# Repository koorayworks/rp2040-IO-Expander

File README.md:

# Wireless Split-Keyboard Module (RP2040-Zero footprint)

A two-board module set that replaces the RP2040-Zero on a split keyboard
and makes the **whole keyboard wireless**: the connection to the PC
(Bluetooth LE) and the left–right link both run on the module board's
nRF52840.

- **Zero board** (`split/zero_board/`): same outline and pinout as a real
  RP2040-Zero (18.0 × 23.5 mm). It is a passive pass-through — no MCU on it.
- **Module board** (`split/module_board/`): carries a Raytac MDBT50Q
  (nRF52840) plus the power circuitry. 18 × 36 mm, 4-layer.
- **Flex** (`split/flex/`): custom 100 mm FPC joining the two boards,
  Hirose FH35C-31S-0.3SHW(50) connectors on both ends, 30 of 31 channels
  used. Pin map: `split/FFC_PINMAP_30P.md` (channel numbers are defined
  by the module-board pads).

## Status — read this first

**Design complete and independently audited. NOT fabricated and NOT
tested on real hardware.**

The design went through several blind audit rounds against primary
sources (datasheets, manufacturer drawings, STEP models). Every defect
found was fixed before fabrication: an unconnected USB VBUS net, an open
flex lane, a connector pin-1 orientation error, sub-spec trace widths.
DRC on the final data: 0 unconnected nets, 0 clearance violations on both
boards. But no physical board has ever been made, so fit (flex mating,
total thickness 0.2 ± 0.03 mm, USB-C position vs. a real Zero) and
electrical behaviour on real hardware are **unverified**. Build at your
own risk; a first article check is strongly recommended.

Manufacturing was planned and fully costed, then shelved: at small lots
the set cannot be produced near the intended price (see
`split/PRICING.md`). The design is released as open hardware instead.

## Power

- Battery: **dry cells, 1–3.3 V input. No LiPo / LiFePO4, no charging.**
- TPS2116 power mux (USB vs. battery), TPS61099 boost to ~3.31 V
  (576k/249k divider), TPS7A2033 LDO.
- MDBT50Q-1MV2 and -P1MV2 share the same footprint and pinout; either
  can be fitted (both TELEC certified).

## Ordering / assembly notes

- Full step-by-step: `split/ORDER_GUIDE.md`; per-board details in each
  board's `PRODUCTION.md`.
- JLCPCB, 4-layer, 1.6 mm, ENIG. Standard PCBA (parts on both sides).
- The Zero board needs the **Castellated Holes** option enabled.
- **U1 (MDBT50Q) is not stocked by JLC.** Use the `*_noU1` BOM/CPL
  variants and hand-mount U1 afterwards. The module ships without a
  bootloader: first flash is via SWD on J5.
- Firmware must set: LFRC `K32SRC_RC` + `K32SRC_500PPM`,
  `CONFIG_GPIO_AS_PINRESET=y`, SAADC acquisition time 40 µs.

## Repository layout

| Path | Contents |
|---|---|
| `SPLIT_SPEC.md` | Frozen specification of the current design |
| `split/zero_board/` | Zero board: KiCad, Gerber zip, BOM/CPL, PRODUCTION.md |
| `split/module_board/` | Module board: KiCad, Gerber zip, BOM/CPL (incl. noU1), PRODUCTION.md |
| `split/flex/` | Flex FPC: generator script, Gerber zip, PRODUCTION.md |
| `split/FFC_PINMAP_30P.md` | The frozen 30-channel pin assignment |
| `split/ORDER_GUIDE.md` | Ordering procedure (6-set first run) |
| `split/PRICING.md` | Cost model and why it was not sold |
| everything at repo root outside `split/` | **Legacy** earlier generations (Rev.W, ext_board). Not the current design. |

## Summary for AI agents

- project: wireless conversion module set for split keyboards (RP2040-Zero replacement)
- form_factor: drop-in replacement for RP2040-Zero (18.0 x 23.5 mm)
- boards: zero_board (passive pass-through), module_board (18 x 36 mm), flex FPC 100 mm
- layers: 4 (both boards), flex 1-layer polyimide
- mcu_module: Raytac MDBT50Q-1MV2 or -P1MV2 (nRF52840), hand-mounted
- connector: Hirose FH35C-31S-0.3SHW(50), 30 channels, pinmap in split/FFC_PINMAP_30P.md
- radio: Bluetooth LE via nRF52840 (host connection and inter-half link)
- power: dry-cell 1-3.3 V in, TPS2116 mux, TPS61099 boost ~3.31 V, TPS7A2033 LDO; no charging
- status: design_complete=true, audited=true, fabricated=false, hardware_tested=false
- manufacturer: JLCPCB PCBA (Standard, both sides), ENIG, castellated holes on zero board
- licence: CERN-OHL-S v2

## Licence

CERN Open Hardware Licence v2 — Strongly Reciprocal (CERN-OHL-S).
See `LICENSE`. If you make and distribute products from this design,
your modified source must stay open under the same licence.

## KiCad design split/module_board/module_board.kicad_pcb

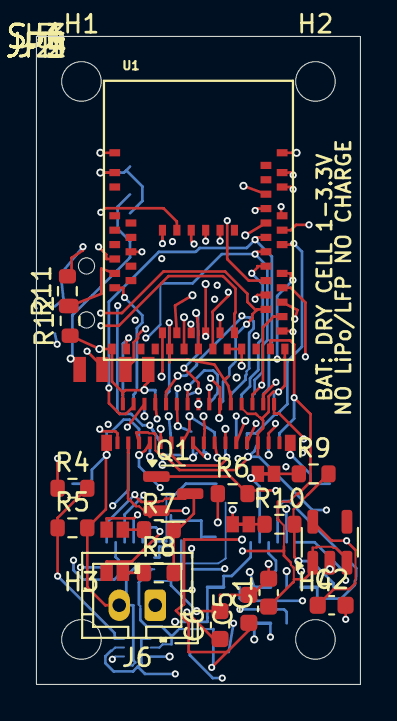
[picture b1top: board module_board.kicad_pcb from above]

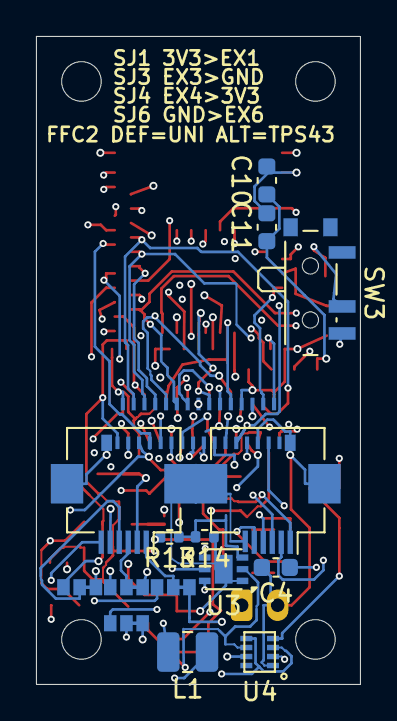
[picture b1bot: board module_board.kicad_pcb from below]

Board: 4 copper layers, 18.0 x 36.0 mm, 43 parts (11 on the bottom side), 58 nets.

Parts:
C1, C2, C4, C10: 10u; C_0603_1608Metric
C5: 22u; C_0603_1608Metric
C6, C11: 100n; C_0603_1608Metric
H1, H2, H3, H4: MountingHole_2.2mm_M2
J1, J2: FH35C-31S-0.3SHW; FH35C-31S
J3, J4: FFC6 TB; Hirose_FH12-6S-0.5SH_1x06-1MP_P0.50mm_Horizontal
J5: SWD; SWD-4P
J6: B2B-PH-K; JST_PH_B2B-PH-K_1x02_P2.00mm_Vertical
JP1, JP2, JP3, JP4: PU-JP; SJ-2P
L1: 2.2uH 2520; L_1008_2520Metric
Q1: AO3401; SOT-23
R4: 180k; R_0603_1608Metric
R5, R6: 100k; R_0603_1608Metric
R7, R8, R9, R10: 4.7k; R_0603_1608Metric
R11, R12: 1M; R_0603_1608Metric
R13: 576k; R_0402_1005Metric
R14: 249k; R_0402_1005Metric
SJ1, SJ3, SJ4, SJ6: SJ; SJ-3P
SW3: PCM12SMTR; SW_SPDT_PCM12
U1: MDBT50Q-1MV2; MDBT50Q
U2: TPS7A2033PDBVR; SOT-23-5
U3: TPS61099DRVR; DFN-6-1EP_2x2mm_P0.65mm_EP1x1.6mm
U4: TPS2116DRLR

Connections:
3V3: C10.1, C11.1, J1.3, J2.3, J5.1, Q1.2, R6.1, R9.2, R10.2, SJ1.1, SJ4.3, U1.28, U1.30, U4.2, U4.7
3V3_BAT: C5.1, R13.2, U3.2, U4.6
3V3_TB: J3.1, Q1.3, R7.2, R8.2
3V3_USB: C2.1, C6.1, R4.1, U2.5, U4.3, U4.5
BAT+: J6.1, SW3.3
BOOST_FB: R13.1, R14.2, U3.3
BOOST_SW: L1.1, U3.5
BOOT: J1.28, J2.28, U1.14
EX1: SJ1.3, U1.48
EX2: J4.2, JP3.1, U1.49
EX3: SJ3.1, U1.50
EX4: SJ4.1, U1.47
EX5: J4.5, JP4.1, U1.19
EX6: SJ6.3, U1.10
FFC2_1: J4.1, SJ1.2
FFC2_3: J4.3, SJ3.2
FFC2_4: J4.4, SJ4.2
FFC2_6: J4.6, SJ6.2
GND: C1.2, C2.2, C4.2, C5.2, C6.2, C10.2, C11.2, J1.2, J1.24, J1.27, J1.32, J1.33, J2.2, J2.24, J2.27, J2.32, J2.33, J3.6, J3.MP, J4.MP, J5.4, J6.2, R5.2, R12.1, R14.1, SJ3.3, SJ6.1, U1.1, U1.2, U1.15, U1.33, U1.55, U2.2, U3.1, U3.7, U4.1
GPIO0: J1.23, J2.23, U1.9
GPIO1: J1.22, J2.22, U1.20
GPIO2: J1.21, J2.21, U1.21
GPIO3: J1.20, J2.20, U1.22
GPIO4: J1.19, J2.19, U1.23
GPIO5: J1.18, J2.18, U1.24
GPIO6: J1.17, J2.17, U1.25
GPIO7: J1.16, J2.16, U1.26
GPIO8: J1.15, J2.15, U1.27
GPIO9: J1.14, J2.14, U1.29
GPIO10: J1.13, J2.13, U1.37
GPIO11: J1.12, J2.12, U1.36
GPIO12: J1.11, J2.11, U1.39
GPIO13: J1.10, J2.10, U1.38
GPIO14: J1.9, J2.9, U1.41
GPIO15: J1.8, J2.8, U1.42
GPIO26: J1.7, J2.7, U1.44
GPIO27: J1.6, J2.6, U1.43
GPIO28: J1.5, J2.5, U1.46
GPIO29: J1.4, J2.4, U1.45
PR1: R4.2, R5.1, U4.4
PU_EX2: JP3.2, R9.1
PU_EX5: JP4.2, R10.1
PU_TB4: JP1.2, R7.1
PU_TB5: JP2.2, R8.1
RESET: J1.29, J2.29, U1.40
STATUS_LED: J1.30, J2.30, U1.16
SWDCLK: J5.3, U1.53
SWDIO: J5.2, U1.51
TB1: Q1.1, R6.2, U1.56
TB2: J3.2, U1.57
TB3: J3.3, U1.58
TB4: J3.4, JP1.1, U1.59
TB5: J3.5, JP2.1, U1.60
USB_D+: J1.26, J2.26, U1.35
USB_D-: J1.25, J2.25, U1.34
VBAT: C4.1, L1.2, R11.2, SW3.2, U3.4, U3.6
VBAT_SENSE: R11.1, R12.2, U1.12
VSYS: C1.1, J1.1, J2.1, U1.32, U2.1, U2.3

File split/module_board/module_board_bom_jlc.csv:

Comment,Designator,Footprint,LCSC Part #
100k,"R5,R6",R_0603_1608Metric,C25803
100nF,"C11,C6",C_0603_1608Metric,C14663
10uF,"C1,C10,C2,C4",C_0603_1608Metric,C96446
180k,R4,R_0603_1608Metric,C22827
1M,"R11,R12",R_0603_1608Metric,C22935
2.2uH shielded 2520,L1,L_1008_2520Metric,C23894
22uF,C5,C_0603_1608Metric,C59461
4.7k,"R10,R7,R8,R9",R_0603_1608Metric,C23162
AO3401A,Q1,SOT-23,C15127
B2B-PH-K (THT),J6,JST_PH_B2B-PH-K_1x02_P2.00mm_Vertical,C131337
FH12-6S-0.5SH,"J3,J4",Hirose_FH12-6S-0.5SH_1x06-1MP_P0.50mm_Horizontal,C202118
FH35C-31S-0.3SHW,J1,FH35C-31S,C424662
MDBT50Q-1MV2,U1,MDBT50Q,C5118826
PCM12SMTR,SW3,SW_SPDT_PCM12,C221841
TPS2116DRLR,U4,TPS2116DRLR,C3235557
TPS61099DRVR,U3,DFN-6-1EP_2x2mm_P0.65mm_EP1x1.6mm,C2842395
576k,R13,R_0402_1005Metric,
249k,R14,R_0402_1005Metric,
TPS7A2033PDBVR,U2,SOT-23-5,C2862740

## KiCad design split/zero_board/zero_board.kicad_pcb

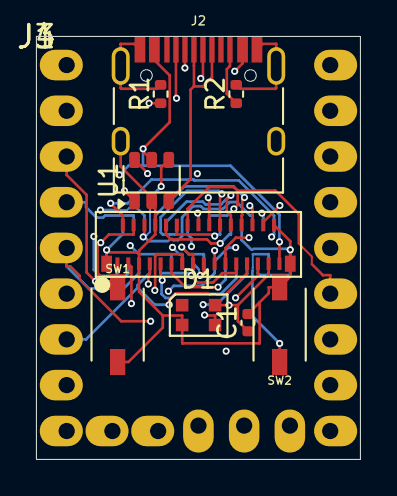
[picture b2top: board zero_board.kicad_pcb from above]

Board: 4 copper layers, 18.0 x 23.5 mm, 11 parts (0 on the bottom side), 32 nets.

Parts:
C1: 100n; C_0402_1005Metric
D1: LED_WS2812B-2020_PLCC4_2.0x2.0mm; LED_WS2812B-2020
J1: ZeroEdge23
J2: TYPE-C-31-M-12
J3, J4: FH35C-31S-0.3SHW; FH35C-31S
R1, R2: 5.1k; R_0402_1005Metric
SW1, SW2: TS-1088-AR02016; SW-SMD_4P-L5.1-W5.1-P3.70-LS6.5-TL_H1.5
U1: USBLC6-2SC6; SOT-23-6

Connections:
3V3: C1.1, D1.4, J1.3, J3.3, J4.3
BOOT: J3.28, J4.28, SW1.1
CC1: J2.A5, R1.1
CC2: J2.B5, R2.1
GND: C1.2, D1.2, J1.2, J2.A1, J2.A12, J2.B1, J2.B12, J2.S1, J3.2, J3.24, J3.27, J3.32, J3.33, J4.2, J4.24, J4.27, J4.32, J4.33, R1.2, R2.2, SW1.2, SW2.2, U1.2
GPIO0: J1.23, J3.23, J4.23
GPIO1: J1.22, J3.22, J4.22
GPIO2: J1.21, J3.21, J4.21
GPIO3: J1.20, J3.20, J4.20
GPIO4: J1.19, J3.19, J4.19
GPIO5: J1.18, J3.18, J4.18
GPIO6: J1.17, J3.17, J4.17
GPIO7: J1.16, J3.16, J4.16
GPIO8: J1.15, J3.15, J4.15
GPIO9: J1.14, J3.14, J4.14
GPIO10: J1.13, J3.13, J4.13
GPIO11: J1.12, J3.12, J4.12
GPIO12: J1.11, J3.11, J4.11
GPIO13: J1.10, J3.10, J4.10
GPIO14: J1.9, J3.9, J4.9
GPIO15: J1.8, J3.8, J4.8
GPIO26: J1.7, J3.7, J4.7
GPIO27: J1.6, J3.6, J4.6
GPIO28: J1.5, J3.5, J4.5
GPIO29: J1.4, J3.4, J4.4
RESET: J3.29, J4.29, SW2.1
STATUS_LED: D1.3, J3.30, J4.30
USB_D+: J3.26, J4.26, U1.4
USB_D+_C: J2.A6, J2.B6, U1.3
USB_D-: J3.25, J4.25, U1.6
USB_D-_C: J2.A7, J2.B7, U1.1
VSYS: J1.1, J2.A4, J2.A9, J2.B4, J2.B9, J3.1, J4.1, U1.5

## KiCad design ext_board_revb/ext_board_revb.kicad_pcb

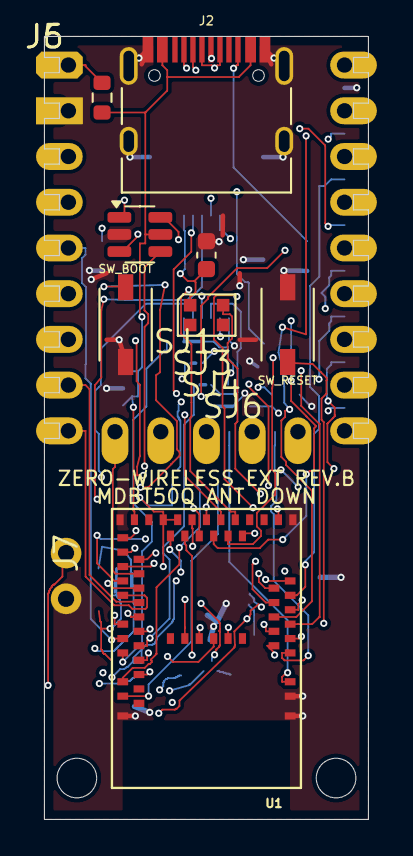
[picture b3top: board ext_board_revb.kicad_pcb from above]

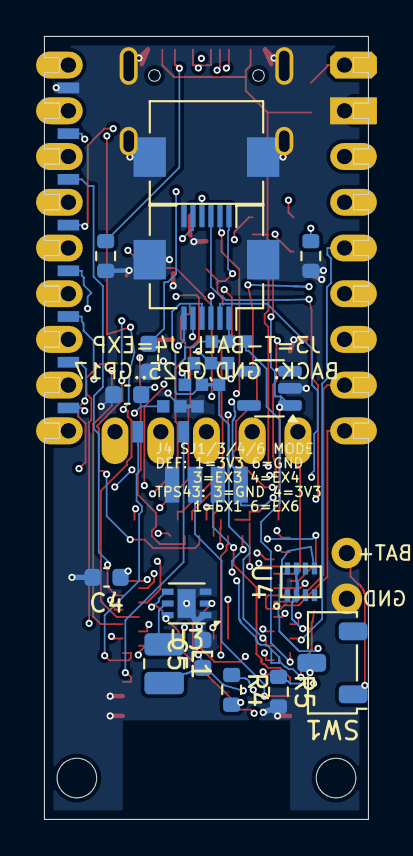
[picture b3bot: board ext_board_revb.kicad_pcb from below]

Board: 4 copper layers, 18.0 x 43.5 mm, 33 parts (19 on the bottom side), 60 nets.

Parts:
C1: 10uF IN; C_0603_1608Metric
C2: 10uF OUT; C_0603_1608Metric
C3: 100nF; C_0603_1608Metric
C4, C5: 10uF 0603; C_0603_1608Metric
D1: USBLC6-2SC6; SOT-23-6
D2: WS2812B-2020; LED_WS2812B-2020_PLCC4_2.0x2.0mm
J2: TYPE-C-31-M-12
J3: FFC6 TB; Hirose_FH12-6S-0.5SH_1x06-1MP_P0.50mm_Horizontal
J4: FFC6 EXP; Hirose_FH12-6S-0.5SH_1x06-1MP_P0.50mm_Horizontal
J5: SWD
J6: BACKPADS GP17-25
J7: BAT THT pads
JLEG: RP2040-Zero-THT; RP2040-Zero-THT-Castellation-Master
L1: 2.2uH 2520; L_1008_2520Metric
MH1, MH2: M2; MountingHole_2.2mm_M2
R1: 5.1k CC1; R_0603_1608Metric
R2: 5.1k CC2; R_0603_1608Metric
R3: 0R VBUS->VSYS; R_0603_1608Metric
R4: 180k 0603; R_0603_1608Metric
R5: 100k 0603; R_0603_1608Metric
SJ1, SJ3, SJ4, SJ6: SJ
SW1: CAS-120A; Nidec_Copal_CAS-120A
SW_BOOT: TS-1088-AR02016; SW-SMD_4P-L5.1-W5.1-P3.70-LS6.5-TL_H1.5
SW_RESET: TS-1088-AR02016; SW-SMD_4P-L5.1-W5.1-P3.70-LS6.5-TL_H1.5
U1: MDBT50Q-1MV2; MDBT50Q
U2: TPS7A2033PDBVR; SOT-23-5
U3: TPS610994DRVR; DFN-6-1EP_2x2mm_P0.65mm_EP1x1.6mm
U4: TPS2116DRLR

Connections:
3V3: C2.1, C3.1, D2.1, J3.1, J4.1, J5.1, JLEG.30, SJ1.2, SJ1.3, SJ4.3, U1.28, U1.30, U4.2, U4.7
3V3_BAT: C5.1, L1.2, U3.2, U4.6
3V3_USB: R4.1, U2.5, U4.3, U4.5
BAT_IN: J7.1, SW1.1
BOOST_SW: L1.1, U3.5
BOOT: SW_BOOT.1, U1.14
CC1: J2.A5, R1.1
CC2: J2.B5, R2.1
EX1: SJ1.1, U1.48
EX2: J4.2, U1.49
EX3: J4.3, SJ3.1, SJ3.2, U1.50
EX4: J4.4, SJ4.1, SJ4.2, U1.47
EX5: J4.5, U1.19
EX6: SJ6.3, U1.10
GND: C1.2, C2.2, C3.2, C4.2, C5.2, D1.2, D2.3, J2.A1, J2.A12, J2.B1, J2.B12, J2.S1, J3.6, J3.MP, J4.6, J4.MP, J5.4, J6.1, J7.2, JLEG.31, R1.2, R2.2, R5.2, SJ3.3, SJ6.1, SJ6.2, SW_BOOT.2, SW_RESET.2, U1.1, U1.2, U1.15, U1.33, U1.55, U2.2, U3.1, U3.3, U3.7, U4.1
GP17: J6.10, U1.3
GP18: J6.9, U1.4
GP19: J6.8, U1.5
GP20: J6.7, U1.6
GP21: J6.6, U1.7
GP22: J6.5, U1.8
GP23: J6.4, U1.11
GP24: J6.3, U1.12
GP25: J6.2, U1.13
GPIO0: JLEG.0, U1.9
GPIO1: JLEG.1, U1.20
GPIO2: JLEG.2, U1.21
GPIO3: JLEG.3, U1.22
GPIO4: JLEG.4, U1.23
GPIO5: JLEG.5, U1.24
GPIO6: JLEG.6, U1.25
GPIO7: JLEG.7, U1.26
GPIO8: JLEG.8, U1.27
GPIO9: JLEG.9, U1.29
GPIO10: JLEG.10, U1.37
GPIO11: JLEG.11, U1.36
GPIO12: JLEG.12, U1.39
GPIO13: JLEG.13, U1.38
GPIO14: JLEG.14, U1.41
GPIO15: JLEG.15, U1.42
GPIO26: JLEG.26, U1.44
GPIO27: JLEG.27, U1.43
GPIO28: JLEG.28, U1.46
GPIO29: JLEG.29, U1.45
PR1: R4.2, R5.1, U4.4
RESET: SW_RESET.1, U1.40
STATUS_LED: D2.4, U1.16
SWDCLK: J5.3, U1.53
SWDIO: J5.2, U1.51
TB2: J3.2, U1.57
TB3: J3.3, U1.58
TB4: J3.4, U1.59
TB5: J3.5, U1.60
USB_D+: D1.4, U1.35
USB_D+_C: D1.3, J2.A6, J2.B6
USB_D-: D1.6, U1.34
USB_D-_C: D1.1, J2.A7, J2.B7
USB_VBUS: C1.1, D1.5, J2.A4, J2.A9, J2.B4, J2.B9, R3.1, U1.32, U2.1, U2.3
VBAT: C4.1, SW1.2, U3.4, U3.6
VSYS: JLEG.32, R3.2

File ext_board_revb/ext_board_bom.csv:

Ref,Qty,Value / Part,Package,Notes
U1,1,"MDBT50Q-1MV2 (Raytac, nRF52840, chip antenna)",MDBT50Q module 10.5x15.5mm,"技適済みモジュール。**ブートローダ書き込み済みのモジュールを購入する前提** (ユーザ方針 2026-10-30)。参考価格 ¥1,243 (スイッチサイエンス, 2026-10-30確認)"
U2,1,"TPS7A2033PDBVR (TI, 3.3V 300mA LDO)",SOT-23-5,裏面実装 (B.Cu)
D1,1,"USBLC6-2SC6 (ST, USB ESD)",SOT-23-6,表面実装
D2,1,"WS2812B-2020 (RGB LED)",PLCC4 2.0x2.0mm,表面実装。本物の LED 位置は近似 (要実物照合)
J2,1,"TYPE-C-31-M-12 (HRO, USB-C receptacle)",USB-C mid-mount,表面実装。マスター基板と同一
J3,1,"FH12-6S-0.5SH (Hirose FFC/FPC 6P 0.5mm)",FFC 6P horizontal,裏面実装。トラックボール用 (TB1-TB6)
J4,1,"FH12-6S-0.5SH (Hirose FFC/FPC 6P 0.5mm)",FFC 6P horizontal,裏面実装。予備 GPIO (EX1-EX6)
SW_BOOT SW_RESET,2,"TS-1088-AR02016 (XUNPU tact switch)",SMD 2P 3.9x3.0mm H2.0,"LCSC C720477 (JLC Basic)。第4ラウンドで 5.1mm 級から交換 (JLEG 干渉解消)。型番 R = 位置決めポストなし。推奨ランド 1.35x1.80 ピッチ 4.15 に対し本基板は 0.85x1.45 にカスタム化 (README_EXT 設計判断 13)"
C1 C2,2,"10uF (ceramic, >=6.3V)",0603,裏面実装。LDO 入出力
C3,1,"100nF (ceramic)",0603,表面実装。LED デカップリング
R1 R2,2,"5.1k ohm",0603,裏面実装。USB-C CC1/CC2 プルダウン (Rd)
R3,1,"0 ohm",0603,表面実装。VBUS -> VSYS 接続ジャンパ
MH1 MH2,2,"M2 hole (no part)",drill 2.2mm NPTH,"基板下端の固定穴。M2 ネジ/スペーサーは別途"
JLEG,1,"Castellation pads (board edge, no part)",-,"ホスト基板へはんだ付け (RP2040-Zero 互換 23 パッド)"
J5,1,"SWD pads (no part)",B.Cu pads 1.27mm pitch,デバッグ用パッド (部品なし)
J6,1,"Back pads GP17-25 (no part)",B.Cu pads,裏面フラットパッド (部品なし)
U3,1,"TPS610994DRVR (TI, 3.3V fixed boost, 0.9V startup)",WSON-6 (DRV) 2x2mm,"裏面実装 (B.Cu)。乾電池 1-3.3V 入力を 3.3V へ昇圧。FB は GND 接続 (固定出力品)"
L1,1,"2.2uH shielded inductor (2520 / 1008 metric)",2520,"裏面実装。TPS61099 推奨値。Isat >= 1A 級を選ぶこと"
C4 C5,2,"10uF (ceramic, >=6.3V)",0603,"裏面実装。昇圧 入力 (C4) / 出力 (C5)"
U4,1,"TPS2116DRLR (TI, power mux, priority mode)",SOT-5X3-8 (DRL),"裏面実装。VIN1=3V3_USB (USB/LDO, 優先), VIN2=3V3_BAT, VOUT=3V3。MODE=VIN1 で priority mode"
R4,1,"180k ohm",0603,"裏面実装。PR1 分圧 (上側)。切替点 VIN1 約 2.8V"
R5,1,"100k ohm",0603,"裏面実装。PR1 分圧 (下側)"
SW1,1,"CAS-120A (Nidec Copal, slide switch SPDT)",SMD 3P,"裏面実装。電池ライン直列スイッチ。ON 方向は実物確認が必要 (README_REVB 参照)"
J7,1,"Battery pads (no connector, THT pads x2)",THT pads 2.54mm pitch,"電池リード直はんだ or 2pin ヘッダ用。JST PH は配置不能のためパッド方式 (README_REVB 参照)。+ 側 = BAT_IN"

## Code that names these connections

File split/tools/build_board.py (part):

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# channel -> net, channel 1 at the left when looking at the populated face
# with the cable exiting downward.
CHANNELS = [
    'VSYS', 'GND', '3V3', 'GPIO29', 'GPIO28', 'GPIO27', 'GPIO26', 'GPIO15',
    'GPIO14', 'GPIO13', 'GPIO12', 'GPIO11', 'GPIO10', 'GPIO9', 'GPIO8',
    'GPIO7', 'GPIO6', 'GPIO5', 'GPIO4', 'GPIO3', 'GPIO2', 'GPIO1', 'GPIO0',
    'GND', 'USB_D-', 'USB_D+', 'GND', 'BOOT', 'RESET', 'STATUS_LED',
]
assert len(CHANNELS) == 30

EDGE = [  # (net, hole_x, hole_y) STEP-verified
    ('VSYS', 1.38, 1.59), ('GND', 1.38, 4.13), ('3V3', 1.38, 6.67),
    ('GPIO29', 1.38, 9.21), ('GPIO28', 1.38, 11.75), ('GPIO27', 1.38, 14.29),
    ('GPIO26', 1.38, 16.83), ('GPIO15', 1.38, 19.37), ('GPIO14', 1.38, 21.92),
    ('GPIO13', 3.92, 21.92), ('GPIO12', 6.46, 21.92), ('GPIO11', 9.00, 21.92),
    ('GPIO10', 11.54, 21.92), ('GPIO9', 14.08, 21.92),
    ('GPIO8', 16.62, 21.92), ('GPIO7', 16.62, 19.37), ('GPIO6', 16.62, 16.83),
    ('GPIO5', 16.62, 14.29), ('GPIO4', 16.62, 11.75), ('GPIO3', 16.62, 9.21),
    ('GPIO2', 16.62, 6.67), ('GPIO1', 16.62, 4.13), ('GPIO0', 16.62, 1.59),
]

board = pcbnew.BOARD()
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edge.SetFPID(pcbnew.LIB_ID('split', 'ZeroEdge23'))
edge.SetReference('J1')
for i, (nname, hx, hy) in enumerate(EDGE, start=1):
    if nname == 'GPIO14':
        dx, dy, sx, sy = 0.30, 0.0, 2.4, 1.7
    elif nname == 'GPIO8':
        dx, dy, sx, sy = -0.30, 0.0, 2.4, 1.7
    elif hx < 9:
        dx, dy, sx, sy = 0.30, 0.0, 2.4, 1.7
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
stub('USB_D-', 11.70, 12.97, 11.70, 13.60)      # J3-25 pad -> south
stub('STATUS_LED', 9.93, 16.38, 9.93, 17.30)    # D1-3 pad -> south
stub('GPIO14', 6.90, 12.97, 6.90, 13.60)        # J3-9 pad -> south (fr13
                                                # left this fanout open)

out = os.path.join(OUT, 'zero_board.kicad_pcb')
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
